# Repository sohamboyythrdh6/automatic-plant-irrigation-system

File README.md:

# automatic-plant-irrigation-system

This project is a fully automatic plant irrigation system designed to water plants only when needed. The system continuously monitors soil moisture levels using a soil moisture sensor and automatically activates a DC water pump when the soil becomes dry.

| Component | Purpose | Qty | Cost (USD) | Distributor |
|-----------|---------|-----|------------|-------------|
| 10k Potentiometer | Adjusts sensitivity | 1 | $0.21 | Maker Bazar |
| IRFZ44N MOSFET | Switches the water pump on and off | 1 | $0.23 | Maker Bazar |
| 10k Through-Hole Resistor | Current limiting and biasing | 2 | $0.32 | Maker Bazar |
| 1N4007 Diode | Protects the circuit from reverse voltage and back EMF | 1 | $0.12 | Maker Bazar |
| 8-Pin IC Socket | Connects the IC to the PCB | 1 | $0.10 | Maker Bazar |
| LM358 IC | Amplifies and processes the sensor signal | 1 | $0.10 | Maker Bazar |
| 12V Water Pump | Pumps water to the plant | 1 | $1.90 | Maker Bazar |
| 2-Pin Screw Terminal Block | Connects external wires | 3 | $0.26 | Maker Bazar |
| Custom PCB | Connects all components together | 1 | $4.00 | JLCPCB |
| Delivery Charges | Shipping costs | 2 | $8.70 | Various |

Unlike many irrigation projects, this design does not use a microcontroller. Instead, it relies on an analog control circuit with a MOSFET for switching the pump, making the system simple, reliable, and power-efficient. The moisture threshold can be adjusted to suit different types of plants and soil conditions.

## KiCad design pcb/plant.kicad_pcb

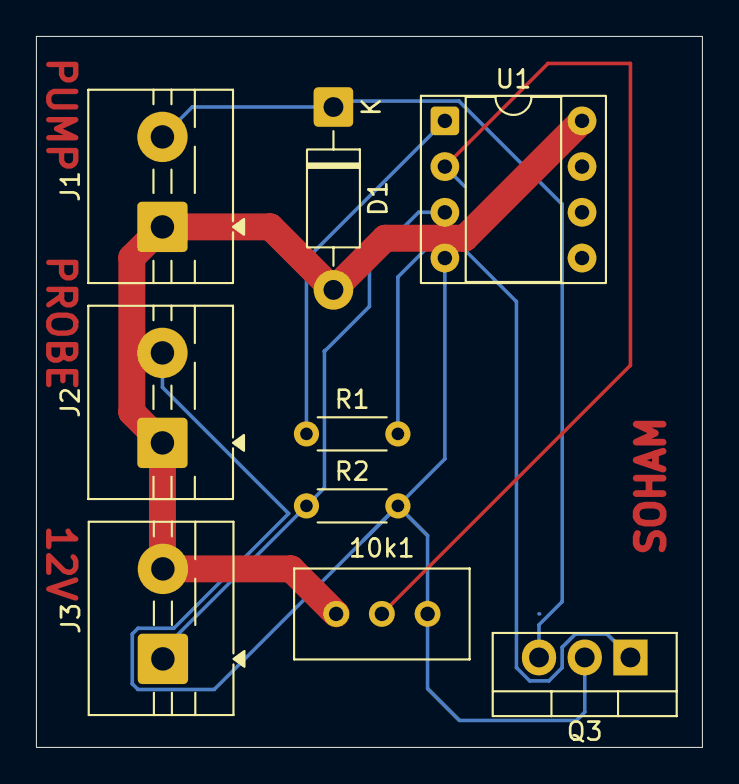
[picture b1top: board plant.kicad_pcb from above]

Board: 2 copper layers, 37.0 x 39.5 mm, 9 parts (0 on the bottom side), 7 nets.

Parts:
10k1: Potentiometer; Potentiometer_Bourns_3296W_Vertical
D1: 1N4001; D_DO-41_SOD81_P10.16mm_Horizontal
J1: water pump; TerminalBlock_MaiXu_MX126-5.0-02P_1x02_P5.00mm
J2: Screw_Terminal_01x02; TerminalBlock_MaiXu_MX126-5.0-02P_1x02_P5.00mm
J3: soil probe; TerminalBlock_MaiXu_MX126-5.0-02P_1x02_P5.00mm
Q3: Q_NMOS_GDS; TO-220-3_Vertical
R1: 1k; R_Axial_DIN0204_L3.6mm_D1.6mm_P5.08mm_Horizontal
R2: 10k; R_Axial_DIN0204_L3.6mm_D1.6mm_P5.08mm_Horizontal
U1: LM358; DIP-8_W7.62mm_Socket

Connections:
unnamed: 10k1.3, D1.2 (A), J1.1, J2.1, J3.2, U1.8 (V+)
unnamed: D1.1 (K), J1.2, Q3.3 (S)
unnamed: 10k1.1, J2.2, Q3.2 (D), R2.2, U1.4 (V-)
unnamed: J3.1, R2.1, U1.3 (+)
unnamed: Q3.1 (G), R1.2
unnamed: R1.1, U1.1
unnamed: 10k1.2, U1.2 (-)

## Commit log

2026-04-18 Create a
2026-04-18 Create assist
2026-04-18 Add bill of materials for project components
2026-06-23 Rename bom to BOM.csv
